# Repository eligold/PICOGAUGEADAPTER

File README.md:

See [BOOSTGAUGE2040](https://www.github.com/eligold/BOOSTGAUGE2040)

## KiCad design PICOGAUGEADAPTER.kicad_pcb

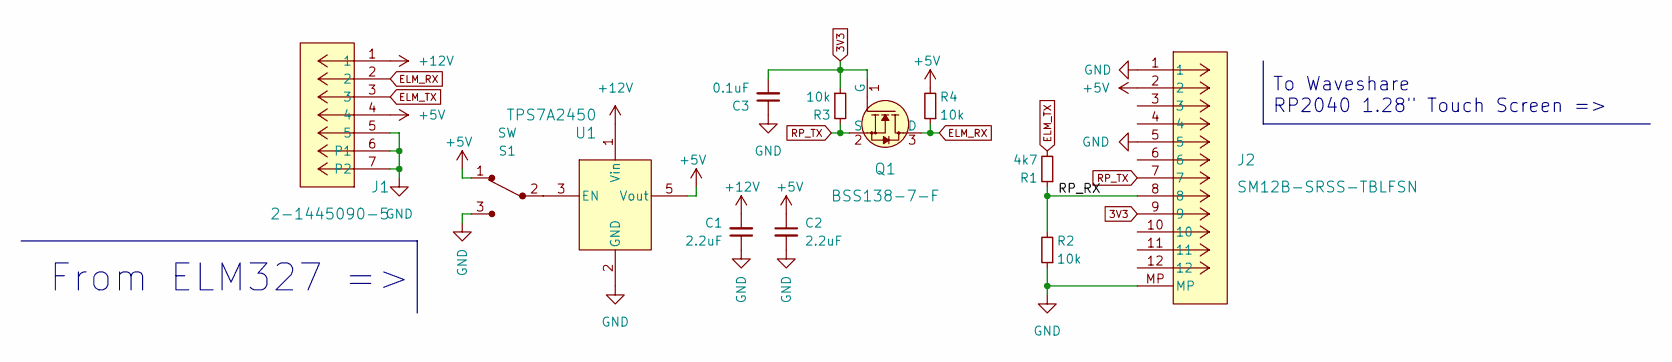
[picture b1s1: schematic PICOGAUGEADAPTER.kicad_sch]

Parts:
C1, C2: 2.2uF; C_0402_1005Metric
C3: 0.1uF; C_0402_1005Metric
J1: 2-1445090-5; 43650-004_05_MOL; MPN 2-1445090-5
J2: SM12B-SRSS-TBLFSN; JST_SH_SM12B-SRSS-TB_1x12-1MP_P1.00mm_Horizontal
Q1: BSS138-7-F; SOT-323; MPN BSS138-7-F; Digi-Key_PN BSS138-FDICT-ND
R1: 4k7; R_0402_1005Metric
R2, R3, R4: 10k; R_0402_1005Metric
S1: SW; SW_SPDT_PCM12; MPN EG1215AA
U1: TPS7A2450; SOT_50DBVR

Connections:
3V3: C3.2, J2.9, Q1.1 (G), R3.1
+5V: C2.1, J1.4, J2.2, R4.2, S1.1, U1.5 (Vout)
+12V: C1.2, J1.1, U1.1 (Vin)
/RP_RX: J2.8, R1.1, R2.2
ELM_RX: J1.2, Q1.3 (D), R4.1
ELM_TX: J1.3, R1.2
GND: C1.1, C2.2, C3.1, J1.5, J1.6 (P1), J1.7 (P2), J2.1, J2.5, J2.MP, R2.1, S1.3, U1.2 (GND)
unnamed: S1.2 (Com), U1.3 (EN)
RP_TX: J2.7, Q1.2 (S), R3.2

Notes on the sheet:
To Waveshare RP2040 1.28" Touch Screen =>
From ELM327 =>

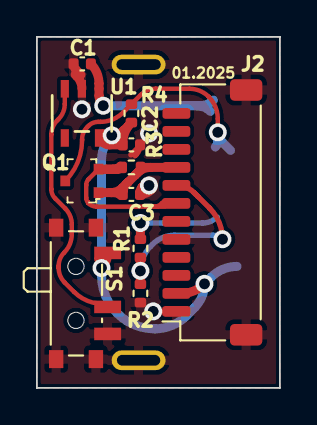
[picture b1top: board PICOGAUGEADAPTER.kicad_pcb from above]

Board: 2 copper layers, 13.5 x 19.5 mm, 12 parts (1 on the bottom side), 9 nets.

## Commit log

2025-03-17 latest for GitHub
2025-03-18 pictures for context
2025-03-31 Create LICENSE
